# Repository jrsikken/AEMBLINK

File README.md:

# AEMBLINK
Design and production files for AEMBLINK, a solar harvesting LED blinking board

Eagle design files: *.sch and *.brd

Bill of Materials: *BOM.xlsx

Gerber files including stencil: *.gerber.zip

Schematic drawing: *SCHEMTAIC.png

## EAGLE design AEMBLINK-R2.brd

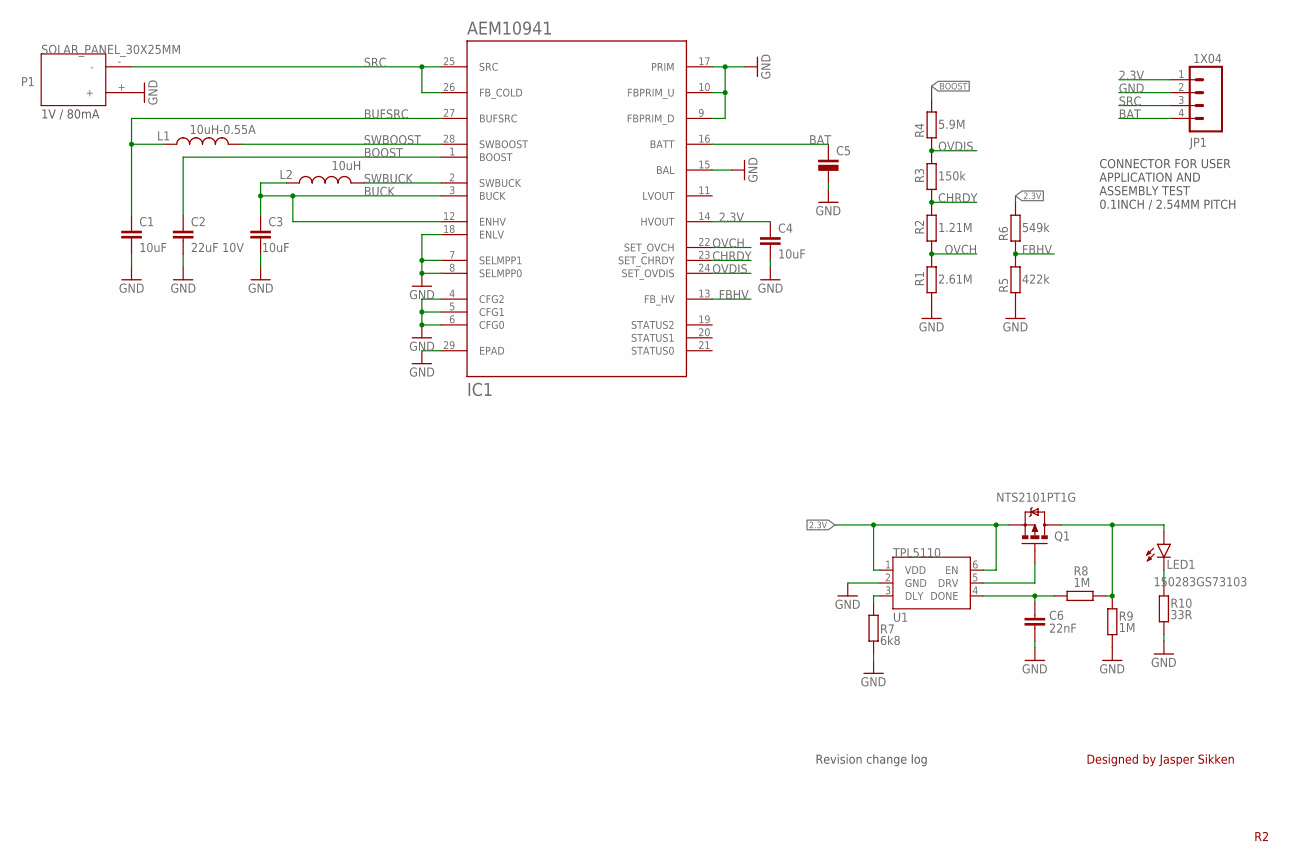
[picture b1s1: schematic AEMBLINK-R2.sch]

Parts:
C1, C3, C4: 10uF; C0603; MPN 1049P
C2: 22uF 10V; C0603; MPN CGA5L1X7S1A226M160AC
C5: SUPERCAPVEL08203R8306G; C_RADIAL_20L8D5P0.8H_HOR
C6: 22nF; C0603
IC1: AEM10941; QFN50P505X505X90-28
JP1: 1X04; 1X04_2.54MM_ROUND_NOSILK
L1: 10uH-0.55A; LPS4012; MPN SRN2009T-100M
L2: 10uH; L0603; MPN CK2125100M-T
LED1: 150283GS73103
P1: SOLAR_PANEL_30X25MM; SOLAR_PANEL_30X25
Q1: NTS2101PT1G; SOT323
R1: 2.61M; R0402
R2: 1.21M; R0402
R3: 150k; R0402
R4: 5.9M; R0402
R5: 422k; R0402
R6: 549k; R0402
R7: 6k8; R0603
R8, R9: 1M; R0603
R10: 33R; R0603
U1: TPL5110; SOT23-6

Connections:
2.3V: C4.1, IC1.14 (HVOUT), JP1.1, Q1.2 (S), R6.2, U1.1 (VDD), U1.6 (EN)
BAT: C5.+, IC1.16 (BATT), JP1.4
BOOST: C2.1, IC1.1 (BOOST), R4.2
BUCK: C3.1, IC1.3 (BUCK), IC1.12 (ENHV), L2.1
BUFSRC: C1.1, IC1.27 (BUFSRC), L1.1
CHRDY: IC1.23 (SET_CHRDY), R2.2, R3.1
DELAY: R7.2, U1.3 (DLY)
DONE: C6.1, R8.1, U1.4 (DONE)
DRIVE: Q1.1 (G), U1.5 (DRV)
FBHV: IC1.13 (FB_HV), R5.2, R6.1
GND: C1.2, C2.2, C3.2, C4.2, C5.-, C6.2, IC1.4 (CFG2), IC1.5 (CFG1), IC1.6 (CFG0), IC1.7 (SELMPP1), IC1.8 (SELMPP0), IC1.9 (FBPRIM_D), IC1.10 (FBPRIM_U), IC1.15 (BAL), IC1.17 (PRIM), IC1.18 (ENLV), IC1.29 (EPAD), JP1.2, P1.+, R1.1, R5.1, R7.1, R9.1, R10.2, U1.2 (GND)
LEDNET: LED1.2 (C), R10.1
unnamed: LED1.1 (A), Q1.3 (D), R8.2, R9.2
OVCH: IC1.22 (SET_OVCH), R1.2, R2.1
OVDIS: IC1.24 (SET_OVDIS), R3.2, R4.1
SRC: IC1.25 (SRC), IC1.26 (FB_COLD), JP1.3, P1.-
SWBOOST: IC1.28 (SWBOOST), L1.2
SWBUCK: IC1.2 (SWBUCK), L2.2

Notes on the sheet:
Designed by Jasper Sikken
Revision change log
CONNECTOR FOR USER APPLICATION AND ASSEMBLY TEST 0.1INCH / 2.54MM PITCH
1V / 80mA

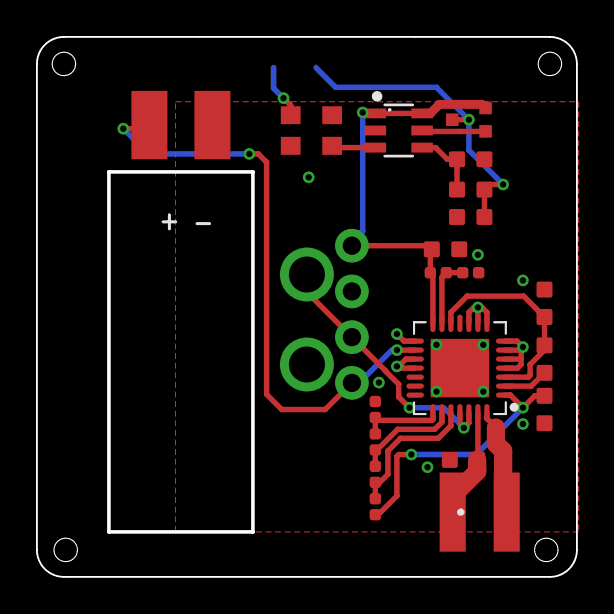
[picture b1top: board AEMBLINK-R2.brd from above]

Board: 2 copper layers, 30.0 x 30.0 mm, 24 parts (1 on the bottom side), 18 nets.

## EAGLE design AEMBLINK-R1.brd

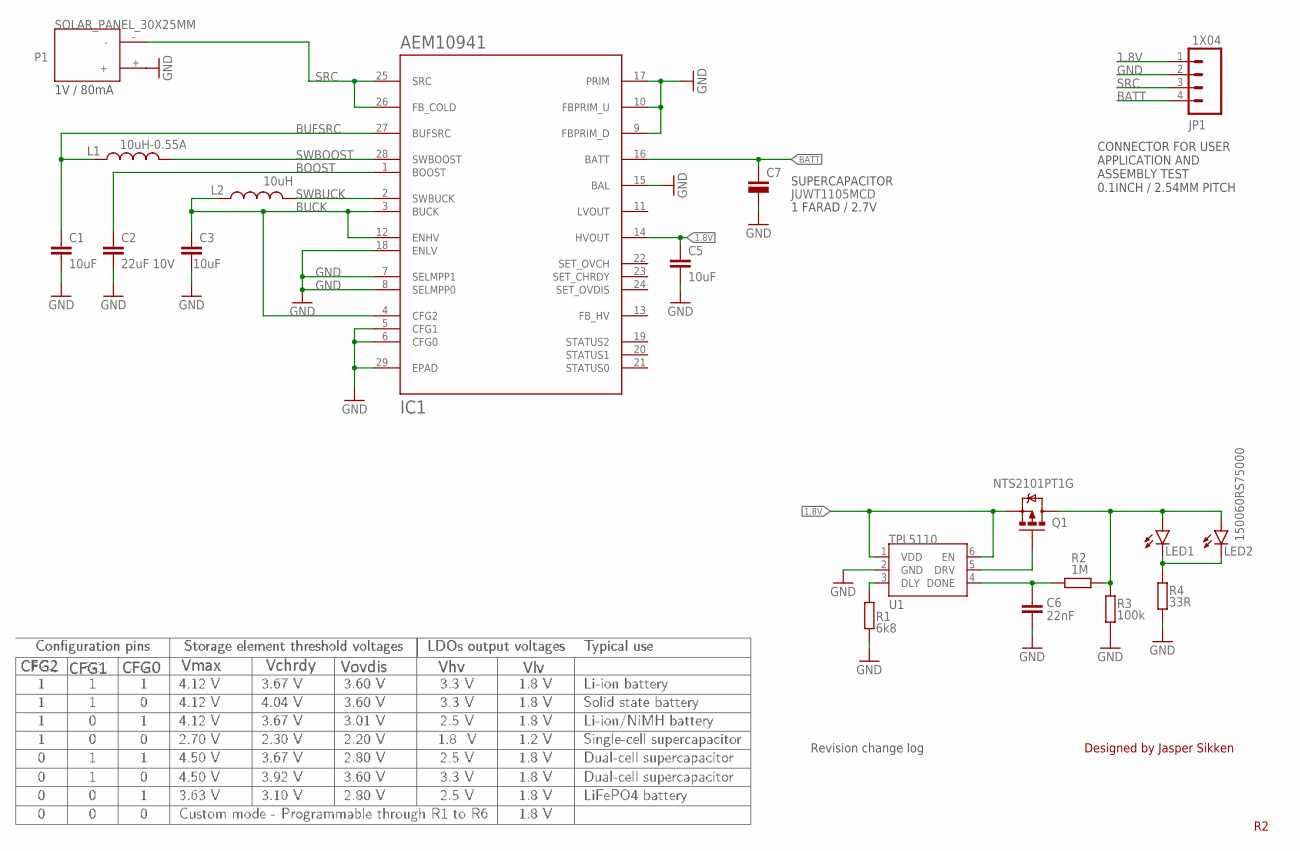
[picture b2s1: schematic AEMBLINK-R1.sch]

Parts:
C1, C3, C5: 10uF; C0603
C2: 22uF 10V; C0603
C6: 22nF; C0603
C7: JUWT1105MCD; C_RADIAL_9L6.3D2.5P0.5H_HOR
IC1: AEM10941; QFN50P505X505X90-28
JP1: 1X04; 1X04_2.54MM_ROUND_NOSILK
L1: 10uH-0.55A; LPS4012
L2: 10uH; L0603
LED1: LEDCHIPLED_0603; CHIPLED_0603
LED2: 150060RS75000; CHIPLED_0603
P1: SOLAR_PANEL_30X25MM; SOLAR_PANEL_30X25
Q1: NTS2101PT1G; SOT323
R1: 6k8; R0603
R2: 1M; R0603
R3: 100k; R0603
R4: 33R; R0603
U1: TPL5110; SOT23-6

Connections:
1.8V: C5.1, IC1.14 (HVOUT), JP1.1, Q1.2 (S), U1.1 (VDD), U1.6 (EN)
BATT: C7.+, IC1.16 (BATT), JP1.4
BOOST: C2.1, IC1.1 (BOOST)
BUCK: C3.1, IC1.3 (BUCK), IC1.4 (CFG2), IC1.12 (ENHV), L2.1
BUFSRC: C1.1, IC1.27 (BUFSRC), L1.1
DELAY: R1.2, U1.3 (DLY)
DONE: C6.1, R2.1, U1.4 (DONE)
DRIVE: Q1.1 (G), U1.5 (DRV)
GND: C1.2, C2.2, C3.2, C5.2, C6.2, C7.-, IC1.5 (CFG1), IC1.6 (CFG0), IC1.7 (SELMPP1), IC1.8 (SELMPP0), IC1.9 (FBPRIM_D), IC1.10 (FBPRIM_U), IC1.15 (BAL), IC1.17 (PRIM), IC1.18 (ENLV), IC1.29 (EPAD), JP1.2, P1.+, R1.1, R3.1, R4.2, U1.2 (GND)
LEDNET: LED1.C, LED2.C, R4.1
unnamed: LED1.A, LED2.A, Q1.3 (D), R2.2, R3.2
SRC: IC1.25 (SRC), IC1.26 (FB_COLD), JP1.3, P1.-
SWBOOST: IC1.28 (SWBOOST), L1.2
SWBUCK: IC1.2 (SWBUCK), L2.2

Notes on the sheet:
Designed by Jasper Sikken
Revision change log
SUPERCAPACITOR
1 FARAD / 2.7V
CONNECTOR FOR USER APPLICATION AND ASSEMBLY TEST 0.1INCH / 2.54MM PITCH
1V / 80mA

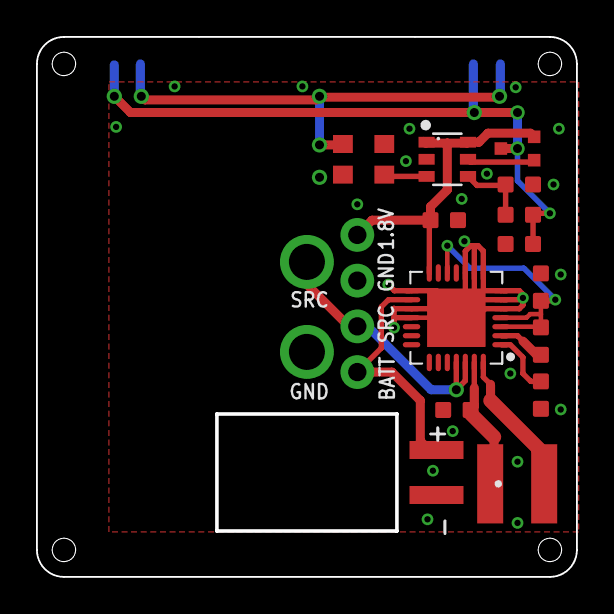
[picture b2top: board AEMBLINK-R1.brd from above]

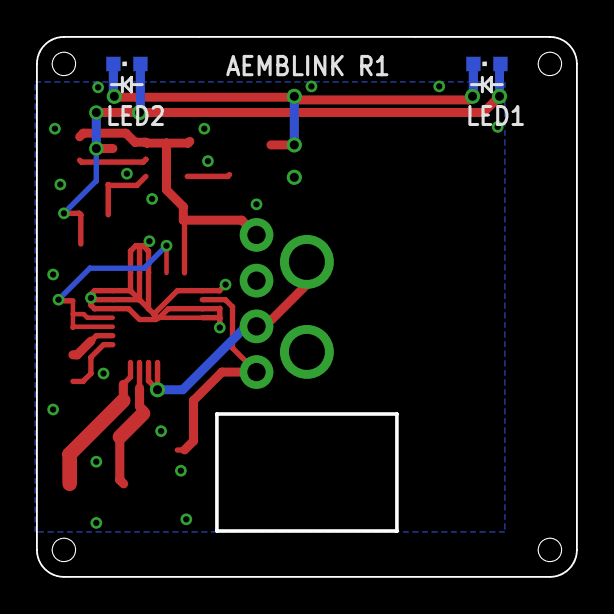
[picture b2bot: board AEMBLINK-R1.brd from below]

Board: 2 copper layers, 30.0 x 30.0 mm, 19 parts (2 on the bottom side), 14 nets.

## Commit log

2019-08-27 First release
2019-08-30 changed R4 from 27R to 33 ohm
2019-08-30 added solar panel and super capacitor
2019-10-01 add gerber files
2019-10-01 correct reame file
2022-09-09 added all R2 files
